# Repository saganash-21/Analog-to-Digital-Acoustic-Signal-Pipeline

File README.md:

# Analog-to-Digital Acoustic Signal Pipeline & Isolated Load Controller
Jeremy Ndirangu

## ⚙️ Executive Summary
This project demonstrates a robust, custom-built analog signal conditioning pipeline designed to extract discrete, reliable logic triggers from a chaotic acoustic environment. To validate the system's industrial applicability, the processed digital signal bridges a mixed-voltage logic gap to control an ESP32 hardware interrupt, which subsequently drives a high-current inductive DC motor.

## 🏗️ System Architecture & Signal Journey
The architecture deliberately avoids monolithic sensor modules in favor of discrete signal conditioning. This ensures absolute control over hysteresis, voltage boundaries, and power isolation across distinct domains.

*   **1. Transducer Stage:** A KY-038 Electret Microphone converts raw physical air pressure into an Alternating Current (AC) wave superimposed on a 1.48V DC baseline.
*   **2. Analog Conditioning Stage:** An operational amplifier is biased with a 10 kΩ voltage divider to establish a 1.65V virtual ground. A 0.1 µF coupling capacitor establishes a 318.3 Hz high-pass filter to block environmental rumble. The signal then passes through a non-inverting amplifier configured with a 101x operational gain, scaling a nominal 20 mV acoustic spike into a 2.2V AC swing.
*   **3. Envelope Detector & Unity Buffer:** A half-wave rectifier diode strips the negative AC wave, charging a parallel RC tank circuit. The 10 µF capacitor and 10 kΩ resistor stretch the microsecond transient into a sustained 0.1-second DC logic envelope, which is then stabilized by a unity gain buffer.
*   **4. Digitizer & Logic Level Bridge:** A Schmitt Trigger configuration establishes a strict upper trip point of 1.05V and a lower trip point of 0.99V to eliminate signal chattering. This generates a clean 1.95V digital edge. A discrete 2N2222 NPN transistor operates as an inverting logic level shifter to bridge the 1.95V signal safely into the 3.3V domain.
*   **5. Firmware Engine (Digital Stage):** `IRAM_ATTR` hardware interrupts on the ESP32 catch the physical digital edge, deploying a mathematical debounce window to reject reverberations.
*   **6. Solid-State Actuation & Protection:** The ESP32 drives an N-Channel MOSFET (M1) via a 330 Ω series resistor, limiting instantaneous inrush current to the parasitic gate capacitance. The MOSFET controls a 5V Brushless DC (BLDC) fan. A 1N4004 flyback diode is placed in parallel across the fan load to provide a safe recirculation path for destructive back-EMF spikes during motor cutoff.
*   **7. Visual Status Indication:** Dedicated Yellow and Green LEDs provide hardware-level diagnostic feedback. Each LED is driven by isolated logic pins and protected by a 220 Ω current-limiting resistor tied directly to ground.

## 📐 Hardware Design Constraints
This system enforces a strict hardware design constraint at the logic bridge: the collector of the NPN transistor is tied to the 3.3V logic domain exclusively via a physical 5.1 kΩ external pull-up resistor. 

Internal microcontroller pull-ups are strictly prohibited in this design architecture. The physical 5.1 kΩ pull-up guarantees a pristine, high-current logic HIGH when the transistor is in cutoff, completely eliminating floating inputs and ensuring industrial-grade signal stability before the hardware interrupt is fired.

## 🧮 Mathematical Design & Schematics
*   **System Mathematics:** Detailed mathematical derivations for the op-amp gain stages, RC time constants, virtual ground bridging, and Schmitt trigger hysteresis are documented in `docs/System_Design_Criteria.pdf`.
*   **Wiring Diagram:** The complete mixed-signal PCB routing drafted in Eagle CAD is available in `schematics/Complete_Circuit_Diagram.pdf`.
*   **System Flow:** The high-level data pipeline mapping is available in `docs/Block_Diagram.png`.

## 💻 Firmware
The C++ logic is entirely interrupt-driven, minimizing processor polling cycles and allowing for concurrent operations. The source code is available in `firmware/main`.

## ## 📊 Bill of Materials
| Stage | Component | Role |
| :--- | :--- | :--- |
| **Transducers** | KY-038 Electret Mic | Acoustic-to-electrical signal conversion. |
| **Analog Pre-Amp** | LM324 Quad Op-Amp | 101x non-inverting gain & virtual ground biasing. |
| **Envelope Detection** | 1N4004 Power Diode | Half-wave rectification for AC-to-DC envelope conversion. |
| **Logic Thresholding** | LM324 Op-Amp | Hysteresis-based Schmitt Trigger digitizer. |
| **Level Shifter** | 2N2222 NPN BJT | Isolated logic translation (1.95V to 3.3V). |
| **Logic Controller** | ESP32 Microcontroller | Interrupt-driven signal processing & state logic. |
| **Power Switching** | IRLZ44N N-Channel MOSFET | Logic-level high-current inductive load control. |
| **Load Protection** | 1N4004 Flyback Diode | Inductive kickback clamping for motor safety. |
| **Actuation** | 5v BLDC Fan | Fan spinning |
| **Diagnostic** | Yellow/Green LEDs | Real-time hardware-level system status indication. |

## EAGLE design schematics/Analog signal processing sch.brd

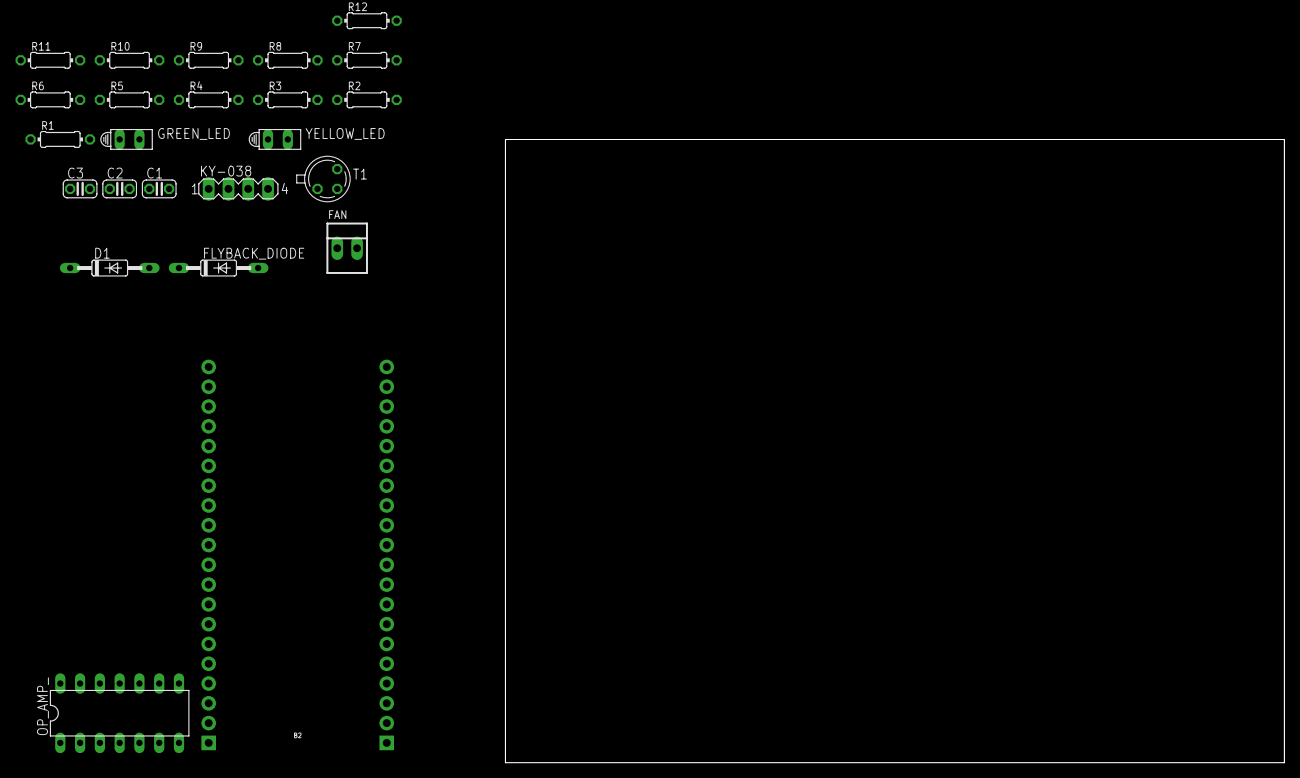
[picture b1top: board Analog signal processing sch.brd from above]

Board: 2 copper layers, 100.0 x 80.0 mm, 24 parts (0 on the bottom side), 20 nets, no tracks yet.

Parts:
B2: ESP 32; ESP32_THING_NO_ANT
C1: 0.1 microF; C025-024X044
C2, C3: 10 microF; C025-024X044
D1: 1N4446; DO35-10
FAN: 5V BLDC FAN; 22-23-2021
FLYBACK_DIODE: 1N4446; DO35-10
GREEN_LED: HLMP6
KY-038: MA04-1
OP_AMP_: LM324N; DIL14
R1, R2, R4, R5, R6, R8, R9: 10k; 0204/7
R3: 100; 0204/7
R7: 15k; 0204/7
R10: 330; 0204/7
R11, R12: 220; 0204/7
T1: 2N2222; TO18
YELLOW_LED: HLMP6

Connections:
+3V3: B2.36, KY-038.3, R1.2, R7.2, R9.1
+5V: FAN.2, FLYBACK_DIODE.C
GND: B2.21, C2.2, KY-038.2, R2.1, R4.1, R6.2, R11.1, R12.1, T1.1
unnamed: C1.2, KY-038.1
unnamed: C1.1, OP_AMP_.3, R1.1, R2.2
unnamed: OP_AMP_.2, R3.1
unnamed: D1.A, OP_AMP_.1
unnamed: C2.1, R3.2
unnamed: C3.1, D1.C, OP_AMP_.5, R4.2
unnamed: OP_AMP_.6, OP_AMP_.7, OP_AMP_.10, R5.2
unnamed: OP_AMP_.8, R5.1, R8.2
unnamed: R8.1, T1.2
unnamed: OP_AMP_.9, R6.1, R7.1
unnamed: B2.14, R9.2, T1.3
unnamed: B2.10, R10.2
unnamed: FAN.1, FLYBACK_DIODE.A
unnamed: B2.15, GREEN_LED.A
unnamed: B2.12, YELLOW_LED.A
unnamed: GREEN_LED.K, R12.2
unnamed: R11.2, YELLOW_LED.K

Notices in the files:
parts and their libraries:
SparkFun-Boards: Licensing: Creative Commons ShareAlike 4.0 International - https://creativecommons.org/licenses/by-sa/4.0
